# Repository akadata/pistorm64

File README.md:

# PiStorm64

PiStorm64 is an Amiga-focused PiStorm fork with ongoing platform, storage, and tooling work.

## Current Highlights

- PiSCSI64 remote disk mount and boot is validated.
- PiSCSI64 ISO-backed CD-ROM mounts are validated.
- Dhrystone has passed 64,000 on the validated Pi4 baseline.
- RTG is functional with a known window-decoration issue under active investigation.
- UAE JIT is still work in progress and is not considered a reliable runtime path yet.

## Read This First

- Main docs index: `docs/README.md`
- Wiki home: `docs/wiki/Home.md`
- PiSCSI64 guide and how-to: `docs/wiki/piscsi64.md`
- Build/install: `docs/wiki/Build-and-Install.md`
- Quickstart: `docs/wiki/Quickstart.md`
- Known issues: `docs/wiki/Known-Issues.md`

## PiSCSI64 Notes

For storage setup, remote mounts, CD-ROM workflow, and operational examples, use:

- `docs/wiki/piscsi64.md`

Windows and macOS client builds exist for the remote tooling, but full validation is still pending.

## DiagROM Credit

**DiagROM is made by John "Chucky" Hertell.**

**We do not take credit for DiagROM.**

Official DiagROM site:

- https://www.diagrom.com

Repository attribution file:

- `DiagROMV2/README.md`

## Third-Party Development Materials

- `amiga.dev/` contains development header/assets integration notes (including
  Picasso96 develop materials). See `amiga.dev/README.md`.
- AmigaOS NDK is **not** shipped in this repository; obtain it from official
  distribution channels and install it locally in your toolchain path.

These are third-party development resources; rights remain with their original
authors/owners.

## ROM/Workbench Media Policy

This repository does **not** ship Amiga ROM images or Amiga Workbench system images.

## Kernel Module Clock Defaults

Use:

```sh
sudo modprobe pistorm gpclk_src=5 gpclk_div=4 run_batch_enable=1 berr_reset_input=1 bus_arb_release=1
```

Changing `gpclk_src` from `5` is not recommended for normal users.

To run emulator without `sudo`, install the udev rule and add your user to the
`pistorm` group:

```sh
sudo groupadd -f pistorm
sudo usermod -aG pistorm "$USER"
sudo cp -f etc/udev/99-pistorm.rules /etc/udev/rules.d/99-pistorm.rules
sudo udevadm control --reload-rules
sudo udevadm trigger
```

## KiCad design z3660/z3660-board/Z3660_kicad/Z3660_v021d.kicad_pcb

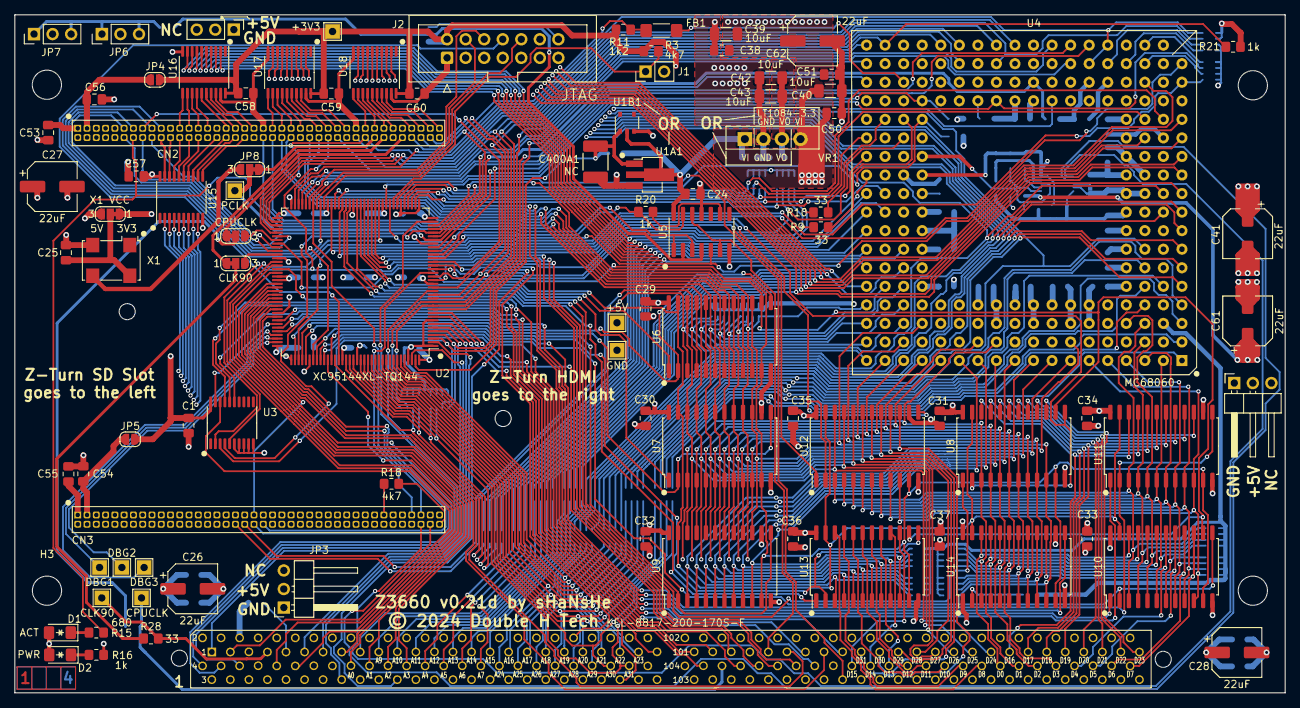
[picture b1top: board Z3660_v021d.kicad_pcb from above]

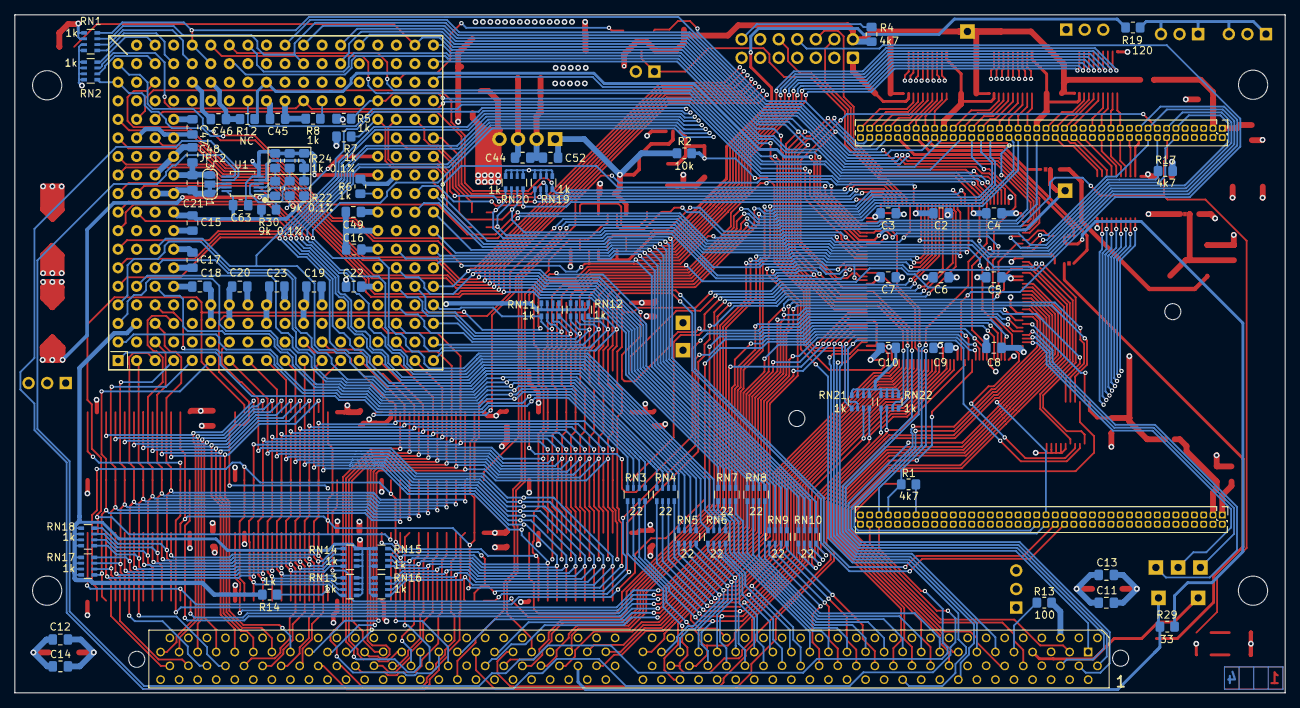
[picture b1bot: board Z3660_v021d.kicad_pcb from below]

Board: 4 copper layers, 173.9 x 92.8 mm, 178 parts (81 on the bottom side), 312 nets.

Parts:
C1, C2, C3, C4, C5, C6, C7, C8, C9, C10, C11, C12, C13, C14, C15, C16, C17, C18, C19, C20, C21, C22, C23, C24, C25, C29, C30, C31, C32, C33, C34, C35, C36, C37, C38, C44, C45, C46, C47, C48, C49, C50, C51, C52, C53, C54, C55, C56, C57, C58, C59, C60, C63: 100nF; C_0805_2012Metric_Pad1.18x1.45mm_HandSolder
C26, C27, C28, C41, C61, C62: 22uF; CP_Elec_6.3x3.9
C39, C40, C42, C43: 10uF; C_1206_3216Metric_Pad1.33x1.80mm_HandSolder
C400A1: NC; C_1812_4532Metric_Pad1.57x3.40mm_HandSolder
CN1: KEL-8817-200-170S-F; xIP-200
CN2, CN3: Conn_02x40_Odd_Even; PinHeader_2x40_P1.27mm_Vertical
D1: LED_Small_Green; LED_1206_3216Metric_Pad1.42x1.75mm_HandSolder
D2: LED_Small_Red; LED_1206_3216Metric_Pad1.42x1.75mm_HandSolder
DBG1, DBG2, DBG3: PCLK; TestPoint_THTPad_2.0x2.0mm_Drill1.0mm
FB1: Ferrite_Bead_Small; Fuse_1806_4516Metric_Pad1.57x1.80mm_HandSolder
H1, H2, H3, H4: MountingHole; MountingHole_4mm
H5, H6, H7, H8: MountingHole; MountingHole_2.2mm_M2
J1: Jumper_2_Open; PinHeader_1x02_P2.54mm_Vertical
J2: Conn_02x07_Odd_Even; IDC-Header_2x07_P2.54mm_Vertical
JP1, JP3: Jumper_NO_Small; PinHeader_1x03_P2.54mm_Horizontal
JP2: Jumper_NO_Small; PinHeader_1x03_P2.54mm_Vertical
JP4, JP5: BRIDGE_3V3; SolderJumper-2_P1.3mm_Open_RoundedPad1.0x1.5mm
JP6, JP7: Jumper_3_Open; PinHeader_1x03_P2.54mm_Vertical
JP8, JP9, JP10, JP11, JP12: SolderJumper_3_Bridged12; SolderJumper-3_P1.3mm_Bridged12_RoundedPad1.0x1.5mm_NumberL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
NT1, NT2, NT3: NetTie_2; NetTie-2_SMD_Pad0.5mm
R1, R3, R4, R17, R18: 4k7; R_0805_2012Metric_Pad1.20x1.40mm_HandSolder
R2: 10k; R_0805_2012Metric_Pad1.20x1.40mm_HandSolder
R5, R6, R7, R8, R14, R16, R20, R21: 1k; R_0805_2012Metric_Pad1.20x1.40mm_HandSolder
R9, R10, R28, R29: 33; R_0805_2012Metric_Pad1.20x1.40mm_HandSolder
R11: 1k2; R_0805_2012Metric_Pad1.20x1.40mm_HandSolder
R12: NC; R_0805_2012Metric_Pad1.20x1.40mm_HandSolder
R13: 100; R_0805_2012Metric_Pad1.20x1.40mm_HandSolder
R15: 680; R_0805_2012Metric_Pad1.20x1.40mm_HandSolder
R19: 120; R_0805_2012Metric_Pad1.20x1.40mm_HandSolder
R22, R26, R27, R30: 9k 0.1%; R_0805_2012Metric_Pad1.20x1.40mm_HandSolder
R23, R24, R25: 1k 0.1%; R_0805_2012Metric_Pad1.20x1.40mm_HandSolder
RN1, RN2, RN11, RN12, RN13, RN14, RN15, RN16, RN17, RN18, RN19, RN20, RN21, RN22: 1k; R_Array_Convex_4x0603
RN3, RN4, RN5, RN6, RN7, RN8, RN9, RN10: 22; R_Array_Convex_4x0603
TP1: +3V3; TestPoint_THTPad_2.0x2.0mm_Drill1.0mm
TP4: +5V; TestPoint_THTPad_2.0x2.0mm_Drill1.0mm
TP8: GND; TestPoint_THTPad_2.0x2.0mm_Drill1.0mm
TP9: PCLK; TestPoint_THTPad_2.0x2.0mm_Drill1.0mm
TP10: CLK90; TestPoint_THTPad_2.0x2.0mm_Drill1.0mm
TP11: CPUCLK; TestPoint_THTPad_2.0x2.0mm_Drill1.0mm
U1: LTC2990; MSOP-10_3x3mm_P0.5mm
U1A1: RH5VA43A; SOT-89-3_Handsoldering
U1B1: BU4942; TSOP-5_1.65x3.05mm_P0.95mm
U2: XC95144XL-TQ144; TQFP-144_20x20mm_P0.5mm
U3, U15, U16, U17, U18: SN74CB3T3245PW; TSSOP-20_4.4x6.5mm_P0.65mm
U4: MC68060; PGA226
U5: 7407; SOIC-14_3.9x8.7mm_P1.27mm
U6, U7, U8, U9, U10, U11, U12, U13, U14: 74FCT543A; SOIC-24W_7.5x15.4mm_P1.27mm
VR1: LT1084-3.3_EXTENDED; Regulador_DCDC
X1: IQXO-70; Oscillator_SMD_IQD_IQXO70-4Pin_7.5x5.0mm

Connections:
3.3V_ZTURN1: C54.1, CN3.3, JP5.1 (A)
3.3V_ZTURN2: C56.1, CN2.3, JP4.1 (A)
040A0: RN10.4 (R4.1), RN22.6 (R3.2), U2.121
040A1: RN10.3 (R3.1), RN22.5 (R4.2), U2.124
040A2: RN10.2 (R2.1), RN21.8 (R1.2), U2.125
040A3: RN10.1 (R1.1), RN21.7 (R2.2), U2.126
040A4: CN1.52 (A4), RN9.4 (R4.1)
040A5: CN1.56 (A5), RN9.3 (R3.1)
040A6: CN1.60 (A6), RN9.2 (R2.1)
040A7: CN1.64 (A7), RN9.1 (R1.1)
040A8: CN1.33 (A8), RN8.4 (R4.1)
040A9: CN1.37 (A9), RN8.3 (R3.1)
040A10: CN1.41 (A10), RN8.2 (R2.1)
040A11: CN1.45 (A11), RN8.1 (R1.1)
040A12: CN1.49 (A12), RN7.4 (R4.1)
040A13: CN1.53 (A13), RN7.3 (R3.1)
040A14: CN1.57 (A14), RN7.2 (R2.1)
040A15: CN1.61 (A15), RN7.1 (R1.1)
040A16: CN1.65 (A16), RN6.4 (R4.1)
040A17: CN1.69 (A17), RN6.3 (R3.1)
040A18: CN1.73 (A18), RN6.2 (R2.1)
040A19: CN1.77 (A19), RN6.1 (R1.1), U2.140
040A20: CN1.81 (A20), RN5.4 (R4.1), U2.139
040A21: CN1.85 (A21), RN5.3 (R3.1), U2.138
040A22: CN1.89 (A22), RN5.2 (R2.1), U2.137
040A23: CN1.93 (A23), RN5.1 (R1.1), U2.136
040A24: CN1.68 (MA24), RN4.4 (R4.1), U2.135
040A25: CN1.72 (MA25), RN4.3 (R3.1), U2.134
040A26: CN1.76 (MA26), RN4.2 (R2.1), U2.133
040A27: CN1.80 (A27), RN4.1 (R1.1), U2.132
040A28: CN1.84 (A28), RN3.4 (R4.1), U2.131
040A29: CN1.88 (A29), RN3.3 (R3.1), U2.130
040A30: CN1.92 (A30), RN3.2 (R2.1), U2.129
040A31: CN1.96 (A31), RN3.1 (R1.1), U2.128
060A0: RN10.5 (R4.2), U4.102 (A0), U16.9 (A7)
060A1: RN10.6 (R3.2), U4.96 (A1), U16.8 (A6)
060A2: RN10.7 (R2.2), U4.89 (A2), U16.7 (A5)
060A3: RN10.8 (R1.2), U4.90 (A3), U16.6 (A4)
060A4: RN9.5 (R4.2), U4.84 (A4), U16.5 (A3)
060A5: RN9.6 (R3.2), U4.78 (A5), U16.4 (A2)
060A6: RN9.7 (R2.2), U4.76 (A6), U16.3 (A1)
060A7: RN9.8 (R1.2), U4.72 (A7), U16.2 (A0)
060A8: RN8.5 (R4.2), U4.66 (A8), U17.9 (A7)
060A9: RN8.6 (R3.2), U4.70 (A9), U17.8 (A6)
060A10: RN8.7 (R2.2), U4.115 (A10), U17.7 (A5)
060A11: RN8.8 (R1.2), U4.111 (A11), U17.6 (A4)
060A12: RN7.5 (R4.2), U4.109 (A12), U17.5 (A3)
060A13: RN7.6 (R3.2), U4.103 (A13), U17.4 (A2)
060A14: RN7.7 (R2.2), U4.97 (A14), U17.3 (A1)
060A15: RN7.8 (R1.2), U4.91 (A15), U17.2 (A0)
060A16: RN6.5 (R4.2), U4.92 (A16), U18.9 (A7)
060A17: RN6.6 (R3.2), U4.85 (A17), U18.8 (A6)
060A18: RN6.7 (R2.2), U4.79 (A18), U18.7 (A5)
060A19: RN6.8 (R1.2), U4.86 (A19), U18.6 (A4)
060A20: RN5.5 (R4.2), U4.73 (A20), U18.5 (A3)
060A21: RN5.6 (R3.2), U4.67 (A21), U18.4 (A2)
060A22: RN5.7 (R2.2), U4.61 (A22), U18.3 (A1)
060A23: RN5.8 (R1.2), U4.75 (A23), U18.2 (A0)
060A24: RN4.5 (R4.2), U4.55 (A24), U15.2 (A0)
060A25: RN4.6 (R3.2), U4.69 (A25), U15.3 (A1)
060A26: RN4.7 (R2.2), U4.62 (A26), U15.4 (A2)
060A27: RN4.8 (R1.2), U4.37 (A27), U15.5 (A3)
060A28: RN3.5 (R4.2), U4.63 (A28), U15.6 (A4)
060A29: RN3.6 (R3.2), U4.19 (A29), U15.7 (A5)
060A30: RN3.7 (R2.2), U4.57 (A30), U15.8 (A6)
060A31: RN3.8 (R1.2), U4.1 (A31), U15.9 (A7)
+3.3VADC: NT2.2, R22.2, R30.2
+3V3: C1.1, C2.1, C3.1, C4.1, C5.1, C6.1, C7.1, C8.1, C9.1, C10.1, C15.1, C16.1, C17.1, C18.1, C19.1, C20.1, C21.1, C22.1, C23.1, C41.1, C42.1, C43.1, C44.1, C45.1, C46.1, C47.1, C48.1, C49.1, C57.1, C58.1, C59.1, C60.1, C63.1, J2.2, JP4.2 (B), JP5.2 (B), JP11.1 (A), JP12.3 (B), NT2.1, R3.2, R4.1, R5.1, R6.1, R7.1, R8.1, R11.2, R14.1, R21.2, R27.2, RN1.1 (R1.1), RN1.2 (R2.1), RN11.1 (R1.1), RN11.2 (R2.1), RN11.3 (R3.1), RN11.4 (R4.1), RN12.1 (R1.1), RN12.2 (R2.1), RN12.3 (R3.1), RN12.4 (R4.1), RN13.1 (R1.1), RN13.2 (R2.1), RN13.3 (R3.1), RN13.4 (R4.1), RN14.1 (R1.1), RN14.2 (R2.1), RN14.3 (R3.1), RN14.4 (R4.1), RN15.1 (R1.1), RN15.2 (R2.1), RN15.3 (R3.1), RN15.4 (R4.1), RN16.1 (R1.1), RN16.2 (R2.1), RN16.3 (R3.1), RN16.4 (R4.1), RN17.1 (R1.1), RN17.2 (R2.1), RN17.3 (R3.1), RN17.4 (R4.1), RN18.1 (R1.1), RN18.2 (R2.1), RN18.3 (R3.1), RN18.4 (R4.1), RN19.1 (R1.1), RN19.2 (R2.1), RN19.3 (R3.1), RN19.4 (R4.1), RN20.1 (R1.1), RN20.2 (R2.1), RN20.3 (R3.1), RN20.4 (R4.1), RN21.1 (R1.1), RN21.2 (R2.1), RN21.3 (R3.1), RN21.4 (R4.1), RN22.1 (R1.1), RN22.2 (R2.1), RN22.3 (R3.1), RN22.4 (R4.1), TP1.1, U1.10 (VCC), U2.1 (VCCIO), U2.8 (VCCINT), U2.37 (VCCIO), U2.42 (VCCINT), U2.55 (VCCIO), U2.73 (VCCIO), U2.84 (VCCINT), U2.109 (VCCIO), U2.127 (VCCIO), U2.141 (VCCINT), U3.20 (VCC), U4.23 (VCC11), U4.27 (VCC12), U4.32 (VCC13), U4.38 (VCC14), U4.41 (VCC23), U4.44 (VCC24), U4.46 (VCC25), U4.48 (VCC26), U4.50 (VCC2), U4.53 (VCC15), U4.74 (VCC16), U4.77 (VCC17), U4.81 (VCC3), U4.82 (VCC4), U4.87 (VCC5), U4.88 (VCC6), U4.100 (VCC7), U4.104 (VCC18), U4.105 (VCC9), U4.107 (VCC19), U4.128 (VCC20), U4.131 (VCC8), U4.134 (VCC0), U4.138 (VCC10), U4.143 (VCC21), U4.152 (VCC1), U4.160 (VCC22), U4.180 (VCC0), U4.181 (VCC0), U4.182 (VCC0), U4.183 (VCC0), U4.184 (VCC0), U4.185 (VCC0), U4.188 (VCC0), U4.189 (VCC0), U4.192 (VCC0), U4.193 (VCC0), U4.195 (VCC0), U4.198 (VCC0), U4.199 (VCC0), U4.207 (VCC0), U15.20 (VCC), U16.20 (VCC), U17.20 (VCC), U18.20 (VCC), VR1.3 (VO)
+5V: C11.1, C12.1, C13.1, C14.1, C24.1, C26.1, C27.1, C28.1, C29.1, C30.1, C31.1, C32.1, C33.1, C34.1, C35.1, C36.1, C37.1, C38.1, C39.1, C40.1, C50.1, C51.1, C52.1, C53.1, C55.1, C61.1, C62.1, CN1.14 (+5V), CN1.15 (+5V), CN1.18 (+5V), CN1.19 (+5V), CN1.22 (+5V), CN1.23 (+5V), CN1.26 (+5V), CN1.27 (+5V), CN1.94 (+5V), CN1.95 (+5V), CN1.98 (+5V), CN1.99 (+5V), CN1.102 (+5V), CN1.103 (+5V), CN1.106 (+5V), CN1.107 (+5V), CN1.174 (+5V), CN1.175 (+5V), CN1.178 (+5V), CN1.179 (+5V), CN1.182 (+5V), CN1.183 (+5V), CN1.186 (+5V), CN1.187 (+5V), CN2.1, CN3.1, D1.2 (A), D2.2 (A), JP1.2, JP2.2, JP3.2, JP6.2 (C), JP7.2 (C), JP11.3 (B), R2.2, R26.2, TP4.1, U1A1.2 (VDD), U1B1.2 (VDD), U5.14 (VCC), U6.24 (VCC), U7.24 (VCC), U8.24 (VCC), U9.24 (VCC), U10.24 (VCC), U11.24 (VCC), U12.24 (VCC), U13.24 (VCC), U14.24 (VCC), VR1.1 (VI), VR1.4 (VI)
/CPU and CLK/SIZ60_0: R10.1, U4.119 (SIZ0)
/CPU and CLK/SIZ60_1: R9.1, U4.118 (SIZ1)
/ZTURN and 3.3V/BP: CN3.80, R18.2
A0: CN1.36 (A0), U2.88
A1: CN1.40 (A1), U2.91
A2: CN1.44 (A2), U2.92
A3: CN1.48 (A3), U2.93
BCLK_FPGA: CN3.39, U2.95
CLK90: CN1.13 (CLK90), R28.2, TP10.1
CLK90_CPLD: JP9.3 (B), U2.83
CLK90_FPGA: CN2.68, JP9.1 (A)
CPUCLK: CN1.112 (CPUCLK), R29.2, TP11.1
CPUCLK_CPLD: JP10.3 (B), U2.79
CPUCLK_FPGA: CN2.72, JP10.1 (A)
CPUCLK_RECVD: CN1.135 (CPUCLKB_RECVD), U2.46
D0: CN1.172 (D0), U10.22 (B0), U14.22 (B0)
D1: CN1.176 (D1), U10.21 (B1), U14.21 (B1)
D2: CN1.180 (D2), U10.20 (B2), U14.20 (B2)
D3: CN1.184 (D3), U10.19 (B3), U14.19 (B3)
D4: CN1.188 (D4), U10.18 (B4), U14.18 (B4)
D5: CN1.192 (D5), U10.17 (B5), U14.17 (B5)
D6: CN1.196 (D6), U10.16 (B6), U14.16 (B6)
D7: CN1.200 (D7), U10.15 (B7), U14.15 (B7)
D8: CN1.168 (D8), U13.22 (B0)
D9: CN1.164 (D9), U13.21 (B1)
D10: CN1.160 (D10), U13.20 (B2)
D11: CN1.156 (D11), U13.19 (B3)
D12: CN1.152 (D12), U13.18 (B4)
D13: CN1.148 (D13), U13.17 (B5)
D14: CN1.144 (D14), U13.16 (B6)
D15: CN1.140 (D15), U13.15 (B7)
D16: CN1.169 (D16), U8.22 (B0), U11.22 (B0)
D17: CN1.173 (D17), U8.21 (B1), U11.21 (B1)
D18: CN1.177 (D18), U8.20 (B2), U11.20 (B2)
D19: CN1.181 (D19), U8.19 (B3), U11.19 (B3)
D20: CN1.185 (D20), U8.18 (B4), U11.18 (B4)
D21: CN1.189 (D21), U8.17 (B5), U11.17 (B5)
D22: CN1.193 (D22), U8.16 (B6), U11.16 (B6)
D23: CN1.197 (D23), U8.15 (B7), U11.15 (B7)
D24: CN1.165 (D24), U6.22 (B0), U7.22 (B0), U9.22 (B0), U12.22 (B0)
D25: CN1.161 (D25), U6.21 (B1), U7.21 (B1), U9.21 (B1), U12.21 (B1)
D26: CN1.157 (D26), U6.20 (B2), U7.20 (B2), U9.20 (B2), U12.20 (B2)
D27: CN1.153 (D27), U6.19 (B3), U7.19 (B3), U9.19 (B3), U12.19 (B3)
D28: CN1.149 (D28), U6.18 (B4), U7.18 (B4), U9.18 (B4), U12.18 (B4)
D29: CN1.145 (D29), U6.17 (B5), U7.17 (B5), U9.17 (B5), U12.17 (B5)
D30: CN1.141 (D30), U6.16 (B6), U7.16 (B6), U9.16 (B6), U12.16 (B6)
D31: CN1.137 (D31), U6.15 (B7), U7.15 (B7), U9.15 (B7), U12.15 (B7)
D040_0: CN3.7, RN18.8 (R1.2), U4.39 (D0), U10.3 (A0), U11.3 (A0), U12.3 (A0)
D040_1: CN3.9, RN18.7 (R2.2), U4.21 (D1), U10.4 (A1), U11.4 (A1), U12.4 (A1)
D040_2: CN3.11, RN18.6 (R3.2), U4.40 (D2), U10.5 (A2), U11.5 (A2), U12.5 (A2)
D040_3: CN3.13, RN18.5 (R4.2), U4.2 (D3), U10.6 (A3), U11.6 (A3), U12.6 (A3)
D040_4: CN3.17, RN17.8 (R1.2), U4.3 (D4), U10.7 (A4), U11.7 (A4), U12.7 (A4)
D040_5: CN3.19, RN17.7 (R2.2), U4.4 (D5), U10.8 (A5), U11.8 (A5), U12.8 (A5)
D040_6: CN3.21, RN17.6 (R3.2), U4.5 (D6), U10.9 (A6), U11.9 (A6), U12.9 (A6)
D040_7: CN3.23, RN17.5 (R4.2), U4.6 (D7), U10.10 (A7), U11.10 (A7), U12.10 (A7)
D040_8: CN3.27, RN16.5 (R4.2), U4.25 (D8), U9.3 (A0), U13.3 (A0)
D040_9: CN3.29, RN16.6 (R3.2), U4.7 (D9), U9.4 (A1), U13.4 (A1)
D040_10: CN3.31, RN16.7 (R2.2), U4.8 (D10), U9.5 (A2), U13.5 (A2)
D040_11: CN3.33, RN16.8 (R1.2), U4.9 (D11), U9.6 (A3), U13.6 (A3)
D040_12: CN3.37, RN15.5 (R4.2), U4.10 (D12), U9.7 (A4), U13.7 (A4)
D040_13: CN3.41, RN15.6 (R3.2), U4.11 (D13), U9.8 (A5), U13.8 (A5)
D040_14: CN3.43, RN15.7 (R2.2), U4.12 (D14), U9.9 (A6), U13.9 (A6)
D040_15: CN3.47, RN15.8 (R1.2), U4.13 (D15), U9.10 (A7), U13.10 (A7)
D040_16: CN3.16, RN14.5 (R4.2), U4.29 (D16), U7.3 (A0), U8.3 (A0), U14.3 (A0)
D040_17: CN3.18, RN14.6 (R3.2), U4.14 (D17), U7.4 (A1), U8.4 (A1), U14.4 (A1)
D040_18: CN3.20, RN14.7 (R2.2), U4.30 (D18), U7.5 (A2), U8.5 (A2), U14.5 (A2)
D040_19: CN3.22, RN14.8 (R1.2), U4.15 (D19), U7.6 (A3), U8.6 (A3), U14.6 (A3)
D040_20: CN3.26, RN13.5 (R4.2), U4.16 (D20), U7.7 (A4), U8.7 (A4), U14.7 (A4)
D040_21: CN3.28, RN13.6 (R3.2), U4.17 (D21), U7.8 (A5), U8.8 (A5), U14.8 (A5)
D040_22: CN3.30, RN13.7 (R2.2), U4.34 (D22), U7.9 (A6), U8.9 (A6), U14.9 (A6)
D040_23: CN3.32, RN13.8 (R1.2), U4.51 (D23), U7.10 (A7), U8.10 (A7), U14.10 (A7)
D040_24: CN3.36, RN12.8 (R1.2), U4.18 (D24), U6.3 (A0)
D040_25: CN3.38, RN12.7 (R2.2), U4.52 (D25), U6.4 (A1)
D040_26: CN2.52, RN12.6 (R3.2), U4.36 (D26), U6.5 (A2)
D040_27: CN2.54, RN12.5 (R4.2), U4.58 (D27), U6.6 (A3)
D040_28: CN2.42, RN11.8 (R1.2), U4.54 (D28), U6.7 (A4)
D040_29: CN2.44, RN11.7 (R2.2), U4.64 (D29), U6.8 (A5)
D040_30: CN2.46, RN11.6 (R3.2), U4.65 (D30), U6.9 (A6)
D040_31: CN2.48, RN11.5 (R4.2), U4.60 (D31), U6.10 (A7)
Earth: C1.2, C2.2, C3.2, C4.2, C5.2, C6.2, C7.2, C8.2, C9.2, C10.2, C11.2, C12.2, C13.2, C14.2, C15.2, C16.2, C17.2, C18.2, C19.2, C20.2, C21.2, C22.2, C23.2, C24.2, C25.2, C26.2, C27.2, C28.2, C29.2, C30.2, C31.2, C32.2, C33.2, C34.2, C35.2, C36.2, C37.2, C38.2, C39.2, C40.2, C41.2, C42.2, C43.2, C44.2, C45.2, C46.2, C47.2, C48.2, C49.2, C50.2, C51.2, C52.2, C53.2, C54.2, C55.2, C56.2, C57.2, C58.2, C59.2, C60.2, C61.2, C62.2, C63.2, C400A1.2, CN1.2 (GND), CN1.3 (GND), CN1.6 (GND), CN1.7 (GND), CN1.10 (GND), CN1.11 (GND), CN1.35 (GND), CN1.38 (GND), CN1.39 (GND), CN1.47 (GND), CN1.50 (GND), CN1.51 (GND), CN1.59 (GND), CN1.62 (GND), CN1.63 (GND), CN1.71 (GND), CN1.74 (GND), CN1.75 (GND), CN1.83 (GND), CN1.86 (GND), CN1.87 (GND), CN1.115 (GND), CN1.118 (GND), CN1.119 (GND), CN1.127 (GND), CN1.130 (GND), CN1.131 (GND), CN1.138 (GND), CN1.139 (GND), CN1.142 (GND), CN1.143 (GND), CN1.151 (GND), CN1.154 (GND), CN1.155 (GND), CN1.163 (GND), CN1.166 (GND), CN1.167 (GND), CN1.190 (GND), CN1.191 (GND), CN1.194 (GND), CN1.195 (GND), CN1.198 (GND), CN1.199 (GND), CN2.2, CN2.4, CN2.20, CN2.21, CN2.30, CN2.31, CN2.40, CN2.41, CN2.50, CN2.60, CN2.61, CN2.70, CN2.71, CN2.80, CN3.2, CN3.4, CN3.24, CN3.25, CN3.34, CN3.35, CN3.44, CN3.54, CN3.67, CN3.68, J1.2 (B), J2.1, J2.3, J2.5, J2.7, J2.9, J2.11, J2.13, JP1.1, JP2.1, JP3.1, JP12.1 (A), NT1.2, R1.2, R12.2, R13.2, R16.1, R17.1, R18.1, R20.2, RN1.3 (R3.1), RN1.4 (R4.1), RN2.1 (R1.1), RN2.2 (R2.1), RN2.3 (R3.1), RN2.4 (R4.1), TP8.1, U1.5 (GND), U1.9 (ADR1), U1A1.3 (GND), U1B1.3 (GND), U2.18 (GND), U2.29 (GND), U2.36 (GND), U2.47 (GND), U2.62 (GND), U2.72 (GND), U2.89 (GND), U2.90 (GND), U2.99 (GND), U2.108 (GND), U2.114 (GND), U2.123 (GND), U2.144 (GND), U3.6 (A4), U3.7 (A5), U3.8 (A6), U3.9 (A7), U3.10 (GND), U4.20 (GND17), U4.22 (GND18), U4.24 (GND19), U4.26 (GND20), U4.28 (GND21), U4.31 (GND22), U4.33 (GND23), U4.35 (GND24), U4.42 (GND3), U4.43 (GND4), U4.45 (GND5), U4.47 (GND6), U4.49 (GND7), U4.56 (GND25), U4.59 (GND26), U4.68 (GND27), U4.71 (GND28), U4.80 (GND29), U4.83 (GND30), U4.93 (GND8), U4.94 (GND9), U4.98 (GND31), U4.99 (GND10), U4.101 (GND32), U4.106 (GND11), U4.110 (GND33), U4.113 (GND34), U4.122 (GND35), U4.125 (GND36), U4.130 (GND12), U4.132 (GND1), U4.136 (GND2), U4.137 (GND13), U4.139 (GND14), U4.146 (GND37), U4.153 (GND0), U4.154 (GND15), U4.159 (GND38), U4.161 (GND39), U4.165 (GND16), U4.170 (DLE), U4.186 (GND3), U4.187 (GND2), U4.190 (GND1), U4.191 (GND0), U4.206 (GND0), U5.7 (GND), U5.9, U5.11, U6.12 (GND), U7.12 (GND), U7.14 (LEAB), U8.12 (GND), U9.12 (GND), U9.14 (LEAB), U10.12 (GND), U11.12 (GND), U11.14 (LEAB), U12.12 (GND), U12.14 (LEAB), U13.12 (GND), U14.1 (LEBA), U14.12 (GND), U14.14 (LEAB), U15.10 (GND), U15.19 (~OE), U16.10 (GND), U16.19 (~OE), U17.10 (GND), U17.19 (~OE), U18.10 (GND), U18.19 (~OE), VR1.2 (GND), X1.2 (GND)
FC0: CN1.20 (FC0), U2.85
FC1: CN1.24 (FC1), U2.86
FC2: CN1.125 (FC2), U2.87
FPGA_PRESENCE: CN2.16, R17.2, U2.82
GNDA: NT1.1, NT3.1, R23.1, R24.1, R25.1
I2C0_CLK: CN3.78, U1.7 (SCL)
I2C0_SDA: CN3.76, U1.6 (SDA)
INT6_ARM: CN3.73, R1.1, U2.21
LEBUS0: U2.52, U6.1 (LEBA)
LEBUS1: U2.53, U7.1 (LEBA)
LEBUS2: U2.54, U8.1 (LEBA)
LEBUS3: U2.56, U9.1 (LEBA)
LEBUS4: U2.57, U13.1 (LEBA)
LEBUS5: U2.58, U12.1 (LEBA)
LEBUS6: U2.59, U11.1 (LEBA)
LEBUS7: U2.60, U10.1 (LEBA)
LEBUS_DMA: U2.34, U6.14 (LEAB), U8.14 (LEAB), U10.14 (LEAB), U13.14 (LEAB)
LED: CN2.14, R15.1, U5.1, U5.3
LEDR: JP6.1 (A), JP6.3 (B), JP7.1 (A), JP7.3 (B), R19.2
unnamed: CN2.22, U15.18 (B0)
unnamed: CN2.23, U16.11 (B7)
unnamed: CN2.24, U15.17 (B1)
unnamed: CN2.25, U16.12 (B6)
unnamed: CN2.26, U15.16 (B2)
unnamed: CN2.27, U16.13 (B5)
unnamed: CN2.28, U15.15 (B3)
unnamed: CN2.29, U16.14 (B4)
unnamed: CN2.32, U15.14 (B4)
unnamed: CN2.33, U16.15 (B3)
unnamed: CN2.34, U15.13 (B5)
unnamed: CN2.35, U16.16 (B2)
unnamed: CN2.36, U15.12 (B6)
unnamed: CN2.37, U16.17 (B1)
unnamed: CN2.38, U15.11 (B7)
unnamed: CN2.39, U16.18 (B0)
unnamed: CN2.43, U17.11 (B7)
unnamed: CN2.45, U17.12 (B6)
unnamed: CN2.47, U17.13 (B5)
unnamed: CN2.49, U17.14 (B4)
unnamed: CN2.53, U17.15 (B3)
unnamed: CN2.55, U17.16 (B2)
unnamed: CN2.57, U17.17 (B1)
unnamed: CN2.59, U17.18 (B0)
unnamed: CN2.63, U18.11 (B7)
unnamed: CN2.65, U18.12 (B6)
unnamed: CN2.67, U18.13 (B5)
unnamed: CN2.69, U18.14 (B4)
unnamed: CN2.73, U18.15 (B3)
unnamed: CN2.75, U18.16 (B2)
unnamed: CN2.77, U18.17 (B1)
unnamed: CN2.79, U18.18 (B0)
unnamed: D1.1 (K), R15.2
unnamed: D2.1 (K), R16.2
unnamed: J1.1 (A), R3.1, U2.44
unnamed: J2.14, R4.2
unnamed: JP9.2 (C), R28.1
unnamed: JP10.2 (C), R29.1
unnamed: C25.1, JP11.2 (C), X1.4 (V+)
unnamed: JP12.2 (C), U1.8 (ADR0)
unnamed: R19.1, U5.2, U5.4
unnamed: RN1.6 (R3.2), U4.149 (TMS)
unnamed: RN1.5 (R4.2), U4.148 (TCK)
unnamed: RN2.8 (R1.2), U4.164 (~TRST)
unnamed: RN2.6 (R3.2), U4.147 (TDI)
unnamed: R23.2, R27.1, U1.1 (V1)
unnamed: R25.2, R26.1, U1.2 (V2)
unnamed: R22.1, R24.2, U1.4 (V4)
unnamed: DBG3.1, U2.105
unnamed: DBG1.1, U2.106
unnamed: DBG2.1, U2.107
unnamed: FB1.2, U4.142 (~TS)
OEBUS0: U2.104, U6.2 (_OEBA), U6.13 (_OEAB)
OEBUS1: U2.110, U7.2 (_OEBA), U7.13 (_OEAB)
OEBUS2: U2.111, U8.2 (_OEBA), U8.13 (_OEAB)
OEBUS3: U2.112, U9.2 (_OEBA), U9.13 (_OEAB)
OEBUS4: U2.113, U13.2 (_OEBA), U13.13 (_OEAB)
OEBUS5: U2.61, U12.2 (_OEBA), U12.13 (_OEAB)
OEBUS6: U2.116, U11.2 (_OEBA), U11.13 (_OEAB)
OEBUS7: U2.120, U10.2 (_OEBA), U10.13 (_OEAB)
PCLK: JP8.2 (C), R12.1, TP9.1, U2.30 (I/O/GCK1), U4.135 (PCLK)
PCLK_FPGA: CN2.66, JP8.1 (A)
PCLK_OSC: JP8.3 (B), X1.3 (OUT)
PS_MIO0: CN2.11, U2.78
PS_MIO8: CN2.13, U2.115
PS_MIO9: CN2.15, U2.20
PS_MIO12: CN2.17, U2.64
PS_MIO13: CN2.19, U2.48
PS_MIO15: CN2.18, U2.81
PUP_4: R14.2, U14.2 (_OEBA)
RESETOUT: R20.1, U2.27, U5.13
R_W: CN1.5 (R_W), U3.18 (B0)
R_W040: CN2.56, RN20.7 (R2.2), U2.19, U3.2 (A0), U4.112 (R_W)
SIZ0: CN1.121 (SIZ0), U2.97
SIZ1: CN1.129 (SIZ1), U2.96
SIZ40_0: CN2.76, R10.2, RN20.5 (R4.2), U2.14
SIZ40_1: CN2.78, R9.2, RN20.6 (R3.2), U2.15
TCK: J2.6, U2.67 (TCK)
TDI: J2.10, U2.63 (TDI)
TDO: J2.8, U2.122 (TDO)
THERM_N: NT3.2, U4.196 (THERM0)
THERM_P: R30.1, U1.3 (V3), U4.197 (THERM1)
TM0: RN19.6 (R3.2), U2.40, U4.114 (TM0)
TM1: RN19.5 (R4.2), U2.39, U4.108 (TM1)
TM2: RN20.8 (R1.2), U2.38 (I/O/GCK3), U4.95 (TM2)
TMS: J2.4, U2.65 (TMS)
TT0: RN19.7 (R2.2), U2.41, U4.117 (TT0)
TT1: RN19.8 (R1.2), U2.43, U4.116 (TT1)
V_DETECTOR: C400A1.1, R2.1, U1A1.1 (~RESET), U1B1.1 (~RESET), U2.143 (I/O/GSR)
_040CIOUT: RN2.5 (R4.2), U2.45, U3.4 (A2), U4.127 (~CIOUT)
_040EMUL: RN1.8 (R1.2), U2.71, U4.150 (~MDIS), U4.166 (~CDIS)
_040IPEND: U3.5 (A3), U4.145 (~IPEND)
_040RSTI: CN2.12, U2.32 (I/O/GCK2), U4.151 (~RSTI)
_040RSTO: U2.25, U4.129 (~RST0), U5.5
_060IPL0: U2.70, U4.169 (IPL0)
_060IPL1: U2.69, U4.168 (IPL1)
_060IPL2: U2.68, U4.167 (IPL2)
_AS: CN1.133 (_AS), U2.117
_AVEC: CN1.12 (_AVEC), U2.16
_AVEC040: U2.76, U4.172 (~AVEC)
_BB040: R21.1, U2.17, U4.178 (~BB)
_BERR: CN1.29 (_BERR), U2.119
_BG: CN1.105 (_BG), U2.101
_BG040: U2.77, U4.174 (~BG)
_BGACK: CN1.8 (_BGACK), U2.94
_BGACK040: U2.102, U3.19 (~OE)
_BGR040: RN2.7 (R2.2), U2.28, U4.208 (~BGR)
_BOSS: CN1.17 (_BOSS), R13.1
_BR: CN1.25 (_BR), U2.6 (I/O/GTS2)
_BR040: U2.11, U4.179 (~BR)
_BTT: R5.2, U2.26, U4.212 (~BTT)
_CEAB: U2.23, U6.11 (_CEAB), U7.11 (_CEAB), U8.11 (_CEAB), U9.11 (_CEAB), U10.11 (_CEAB), U11.11 (_CEAB), U12.11 (_CEAB), U13.11 (_CEAB), U14.11 (_CEAB)
_CEBA: U2.80, U6.23 (_CEBA), U7.23 (_CEBA), U8.23 (_CEBA), U9.23 (_CEBA), U10.23 (_CEBA), U11.23 (_CEBA), U12.23 (_CEBA), U13.23 (_CEBA), U14.23 (_CEBA)
_CIIN: CN1.132 (_CIIN), U2.10
_CIOUT: CN1.101 (_CIOUT), U3.16 (B2)
_CLA: R6.2, U4.194 (~CLA)
_CLKEN: CN3.75, U2.66, U4.205 (~CLKEN)
_CPURST: CN1.109 (_CPURST), U2.9
_DMACOE: U2.103, U14.13 (_OEAB)
_DS: CN1.97 (_DS), U2.118
_DSACK0: CN1.91 (_DSACK0), U2.7
_DSACK1: CN1.1 (_DSACK1), U2.5 (I/O/GTS1)
_EMUL: CN1.31 (_EMUL), U2.2 (I/O/GTS3)
_HLT: CN1.4 (_HLT), U2.35
_INT2: CN1.82 (NC), U2.24
_INT6: CN1.43 (NC), U2.22
_IPEND: CN1.116 (_IPEND), U3.15 (B3)
_IPL0: CN1.120 (_IPL0), U2.49
_IPL1: CN1.124 (_IPL1), U2.50
_IPL2: CN1.128 (_IPL0), U2.51
_LOCK: RN21.6 (R3.2), U2.3 (I/O/GTS4), U3.3 (A1), U4.162 (~LOCK)
_LOCKE: RN21.5 (R4.2), U2.4, U4.144 (~LOCKE)
_RESET: CN1.117 (_RESET), U5.6, U5.12
_RMC: CN1.108 (_RMC), U3.17 (B1)
_SNOOP: R7.2, U2.33, U4.200 (~SNOOP)
_STERM: CN1.21 (_STERM), U2.142
_TA: CN2.58, RN22.7 (R2.2), U2.12, U4.175 (~TA)
_TBI: RN1.7 (R2.2), U2.75, U4.155 (~TBI)
_TCI: CN2.64, U2.74, U4.171 (~TCI)
_TEA: CN2.62, RN22.8 (R1.2), U2.13, U4.157 (~TEA)
_TRA: R8.2, U4.209 (~TRA)
_TS: CN2.74, FB1.1, R11.1, U2.31
nTBI_FPGA: CN3.42, U2.98
nTS_FPGA: CN3.40, U2.100

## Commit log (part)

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2026-01-29 fixed many warnings
2026-01-29 many io and buffer fixes
2026-01-30 full wiki
2026-01-30 base FC line and CPLD .md
2026-01-30 add z3bus skeleton and roadmap
2026-01-30 add zorro devices, crypto backend, and amiga docs
2026-01-30 z3bus is alive
2026-01-30 fix zorro build and link openssl
2026-01-30 avoid root rebuild in kernel_install
2026-01-30 clean branch
2026-01-30 added lemarux-pistorm-firmware, somwehere the truth exists
2026-01-30 fix: stub piscsi cpu dump when debug off
2026-01-30 amiga: add pissa/pissl tools and make targets
2026-01-30 reverted default.cfg to enable new z3bus setvar
2026-01-31 made RTG_MEM Dynamic and fixed issue where ssh term and CTRL+C were blocked
2026-01-31 clean branch, does RTG really take SSH keyboard control?
2026-01-31 added benchmark results
2026-02-05 initial Atari remergein
2026-02-05 Kernel PiStorm64 shines like FC BERR with a Custom CVF build!
2026-02-05 added source and amiga binary for kbdlog and kbdlog.c this is to learn the Amiga keycodes reset for the three finger reset
2026-02-05 Only the Amiga makes it possible! impossible fc_lines added, new CPLD code and docs and compile information!, lets build
2026-02-06 JIT WIP - semi boot memory issues
2026-02-06 update test .v file
2026-02-06 Allow JIT low-memory mapped access
2026-02-06 Clarify Pi4-only clocking and test coverage
2026-02-06 Add syslog logging option
2026-02-06 closer but broken still
2026-02-06 code working here --jit does not boot with pc errors
2026-02-07 last tests timeout
2026-02-07 jit almsot booted
2026-02-07 still nope
2026-02-07 extra surces to be removed soon
2026-02-07 Document UAE JIT source parity guidance
2026-02-07 Fix jff_DIVLS32 remainder sign correction
2026-02-07 Adjust reset jump bias and add reset tracing
2026-02-07 Enable DIVL/SUBX JIT entries
2026-02-07 added amiberry-lite as amiberry jit is said to be a tad broken
2026-02-07 Import Amiberry-Lite JIT sources
2026-02-07 Add UAE fpp_native.cpp prebuild rule
2026-02-07 Add reset trace details for UAE CPU
2026-02-07 removed sources
2026-02-07 Add zfile sources to UAE build
2026-02-07 Clean up unused UAE CPU helpers
2026-02-07 Remove amiberry-lite build deps for UAE JIT
2026-02-08 fubar
2026-02-09 merged jit - getting closer
2026-02-09 removed buffee
2026-02-09 MMU baby illegal instructions happen
2026-02-10 autoconf tidy
2026-02-10 updated log.c ,.h etc
2026-02-11 extram 2.2gb max test
2026-02-11 oops pistorm.conf had wrong clk pin
2026-02-12 full cpu state implimented and tested
2026-02-12 65699 Dhrystones.
2026-02-12 63k dhrystones;
2026-02-12 added piscsi64 yay cd iso we will have
2026-02-12 piscsi64 cdrom support
2026-02-13 wip video rtg64 pause
2026-02-13 Update copyright year in LICENSE file
2026-02-13 Enhance SECURITY.md with detailed reporting guidelines
    Expanded the security policy to include detailed sections on supported projects, reporting vulnerabilities, and expectations for reporters. Added guidelines for responsible disclosure and clarified w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
2026-02-13 Create CONTRIBUTING.md with guidelines for contributors
    Add contributing guidelines for the PiStorm64 project, including project philosophy, scope, coding style, and testing requirements.
2026-02-13 basic net64 support
2026-02-13 piscsi64 disk mount works! take care with bootable flag and priority or booting is fun! still thats super duper fast local disks
2026-02-13 ro rw disk mount succeeded tested, validated. gofaster stripes
2026-02-14 piscsi64: add TLS-secured remote backend and refresh docs
    Achievements:\n- Added TLS-PSK transport for PiSCSI64 remote disk traffic using OpenSSL on both Pi backend and remote server/client tools.\n- Removed cleartext token exchange from protocol payload (t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
2026-02-14 ready to merge
2026-02-14 docs: refresh status/wiki and add DiagROM attribution
    - Rewrite docs/README.md as current index and project status snapshot
    - Add root README.md with current highlights and links
    - Update wiki pages for PiSCSI64 milestones, JIT WIP status, and RTG known issue
    - Remove outdated gpclk_src=6 guidance; keep gpclk_src=5/gpclk_div=6 baseline
    - Normalize user-specific paths to /home/smalley/smalley in docs and tools text
    - Set TAP netdev defaults to User/Group pistorm in etc/systemd/network/30-tap0-amiga.netdev
2026-02-14 docs: state that AmigaOS NDK is not bundled in repo
2026-02-14 Ignore local NDK directory
2026-02-14 found HDToolBox bug, SCSI ID > 8<16 confirmed OK . HDToolBox can not see it so format on a low ID remount on a high ID
2026-02-14 LBA fun, dont try over 48GB in a single partition maemory may become an issue and overlap on itself. Amiga reports full disk size, while unless blocksize=4096 disks will wrap with CHS vs LBA issues, 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
2026-02-15 added remotes
2026-02-15 refactor pigfx - segfault - add old code to compare
2026-02-15 rtg: keep P96 blit coordinates signed and clip negative origins
2026-02-15 rtg: replace minterm macro with typed helpers
2026-02-15 rtg/raylib: stabilize frame state reads during mode switches
2026-02-18 removed bin/adfmanager.py while we fix the CodeQL issues
2026-02-18 resolved CodeQL 0.0.0.0 binds a socket to all interfaces.
2026-02-18 clean up and add extra a314 code
2026-02-19 core-rtg
2026-02-20 core-rtg title bar only
2026-02-20 removed old refereced files
2026-02-20 step 0 replace //{ with {//
2026-02-20 last //{ in src/musashi/m68kfpu.c
2026-02-20 what happened, we broke. this should be good
2026-02-20 works
2026-02-20 reveted pistorm.hdf drivers
2026-02-21 rtg and fakenativemode almost rworking nicely, , however can totally rip our iRTG and all that goes with it and reduce rtg.c by around 50% code size!.. umm
2026-02-21 rtg working nicely however 5-10 FPS only
2026-02-21 RTG rock solid stable 1080p 16 bit 70+ FPS
2026-02-21 RTG is rocking its way towards main branch
2026-02-22 FAKENATIVEMODE=256COL on ECS ChipSet and Doom2 plays properly 60FPS+
2026-02-22 PiRTG64
2026-02-22 remved .git-rewrite
2026-02-22 060 test with jit fail pause
2026-02-22 go slow
2026-02-22 tidy up
2026-02-22 resolved socket garb crashed internet
2026-02-22 updated shader location
2026-02-22 header fallout fix
2026-02-23 working configs, 68040 seems to have issues;
2026-02-24 We let go of the bus, 299935 Dhrystones and custom chips tell PiStorm what to do!!!!!
2026-02-24 CPLD: bus relinquish experiment; SysInfo milestone
    SysInfo 4.5b12 results (no JIT / no Emu68):
    - 369,692 Dhrystones
    - 386.89 MIPS
    - 198.33 MFLOPS
    - ~5.33x chip RAM speed
    Notes:
2026-02-24 repo tidy
2026-02-24 lost piscsi64 boot.rom features while fixing pissl
2026-02-24 broken
2026-02-25 WORKING
2026-02-26 /pistorm.hdf latest
2026-02-26 removed legacy -lvcos -lvchiq_arm -lbcm_host build options
2026-02-27 updated Makefile
2026-02-28 piscsi64 migrated and backported to piscsi
2026-02-28 piscsi has cdrom and remote support
2026-02-28 need to fix autoconf memory overlaps
2026-02-28 removed old log files
2026-02-28 clean working branch main piscsi with cdrom and remote
2026-03-03 ble0
2026-03-04 ppc test 10/10 success
2026-03-04 ppc: stage2 execution proof (counter loop), NIP/instr sanity, startup watchdog
2026-03-04 stage3 benchmark bench: iters=100000 warmup=1000 elapsed=0.013s ops/s=7422912 avg_us=0.13
2026-03-04 stage4 complete
2026-03-04 stage 5b complete
2026-03-04 Stage 6B: canonical PPC accel ABI + Amiga IRQ/doorbell test
2026-03-04 stage 6c complete
2026-03-04 stage6b: unify ABI header, add ppcshake --irq, harden tool single-instance
2026-03-04 ppc board seen as version 0 will affect ppcvision
2026-03-05 ppc-accel: add qemu log forwarding and IO callback tracing
2026-03-06 ppc-accel: gate diag bootpoint start behind explicit env
2026-03-06 ppc-accel: expose boot descriptor via control registers
2026-03-06 ppc-accel: add descriptor branch boot-test via ppcshake
2026-03-06 ppcshake boot test works stage 1,2 boot OK
2026-03-07 updated Mountlist for pi0-4 and pd0-4 adf floppy
2026-03-07 amiga: restore legacy autoconfig access and decouple A314 mem window
2026-03-07 clean build tree
2026-03-07 updated default.cfg to guard against uae-ppc.so deps
2026-03-08 armaccel.v0
2026-03-08 pistorm: keep kmod default, add optional userspace-mmio backend; restore safe CPLD baseline
2026-03-08 merged userspace pistorm back into main , no longer need pistorm.ko 5% boost
2026-03-09 jump Program execution from 33% to 40$ and Memory copy to 72%
2026-03-09 userspace-mmio: add chip-ram sequential write mode (PISTORM_MMIO_RAMSEQ) and keep default safe toggles
2026-03-09 userspace-mmio: conservative wpipe (fc=0 chip-ram only) and improved chip memcpy to 74%
2026-03-09 performance tweaks
2026-03-14 JIT Comes up with PISCSI Boot - No Kickstart or Z3 ram yet
2026-03-14 fatal test results
2026-03-14 a314 feature complete
2026-03-15 added tools and libs hdf, and now 68k cpu correctness tests
2026-03-15 added 680x0TestSuite-Phase1
2026-03-15 First XFAIL is cleared: bfext now passes and Stage1 CI passes with only 3 remaining XFAILs
2026-03-15 bfset is fixed and now passes.
2026-03-15 cmp2 is fixed, and Stage1 68040 is now fully green.
2026-03-15 musashi: handle 68040 PCR MOVEC in both directions
2026-03-15 musashi: default PCR ID to 430 with env override
2026-03-15 Revert "musashi: handle 68040 PCR MOVEC in both directions"
    This reverts commit 27f5045ee88c015dab34268bdabe16491a99c625.
2026-03-15 docs: add 680x0 phase1 status report and harness runbook
2026-03-15 make processortests-quick passed (files=124 tests=992 transactions=5097 errors=0) - make stage1-680x0-ci passed - quick: pass=4 fail=0 - 68040: pass=18 fail=0 xfail=0 xpass=0
2026-03-15 stage0 jit wiring
2026-03-17 a night of jit progress - not quite there yet
2026-03-17 JIT Booted and got to workbench
2026-03-19 ontrack0
2026-03-20 latest jit wip
2026-03-20 musashi: revert branch-local changes back to main baseline
2026-03-20 jit: fix AArch64 emitter encodings for W ops and CBZ/CBNZ
2026-03-20 jit: route control-flow opcode families through Musashi fallback
2026-03-20 jit: fix 68040 MOVEC decode and control register handling
2026-03-20 jit: stage 68040 internal FPU model and selection logic
2026-03-20 jit: add staged validation checkpoints for 68040 JIT
2026-03-20 jit: remove env gating from configured m68xkcpu execution path
2026-03-20 jit: harden hot-pc eviction and fallback discipline
2026-03-20 jit: document decoded hot-path kickstart loops
2026-03-20 jit: seed x19 cpu pointer before host block execution
2026-03-20 jit: boost fallback slices when interpret-loop signatures repeat
2026-03-20 jit: keep low vector-space PCs on musashi fallback path
2026-03-20 jit: narrow compiled families and default fast-step for semantic safety
2026-03-20 jit: keep fast-step opt-in while fallback semantics are stabilized
2026-03-20 jit: remove pre-gating and loop-boost masking; return positive block cycles
2026-03-20 jit: fix ADD/CMP decode and write back 68k flags from NZCV
2026-03-20 jit: route translated guest memory accesses through bus helpers
2026-03-20 jit: fix branch taken PC writeback double-increment
2026-03-20 jit: fix bcc/bxx skip offsets in branch translator
2026-03-20 jit: default to strict no-fallback mode and neutralize core init banner
2026-03-21 build: add USE_MUSASHI gate and enforce JIT-only mode
2026-03-21 build: fix musashi header resolution and stop repeated m68kmake runs
2026-03-21 build: gate kmod backend sources behind PISTORM_KMOD
2026-03-21 build: gate PMMU define behind USE_MUSASHI
2026-03-21 jit: fix Bcc/BRA retirement semantics in AArch64 branch translator
2026-03-21 jit: fix LEA extension-word decode in block translation
2026-03-21 jit: preserve CMP destination across helper reads
2026-03-21 jit: preserve ADD/SUB destination across helper reads
2026-03-21 jit: fix MOVE size-bit decode mapping

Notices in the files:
z3660/z3660-board/Z3660_kicad/Z3660_v021d.kicad_pcb:
© 2024 Double H Tech
